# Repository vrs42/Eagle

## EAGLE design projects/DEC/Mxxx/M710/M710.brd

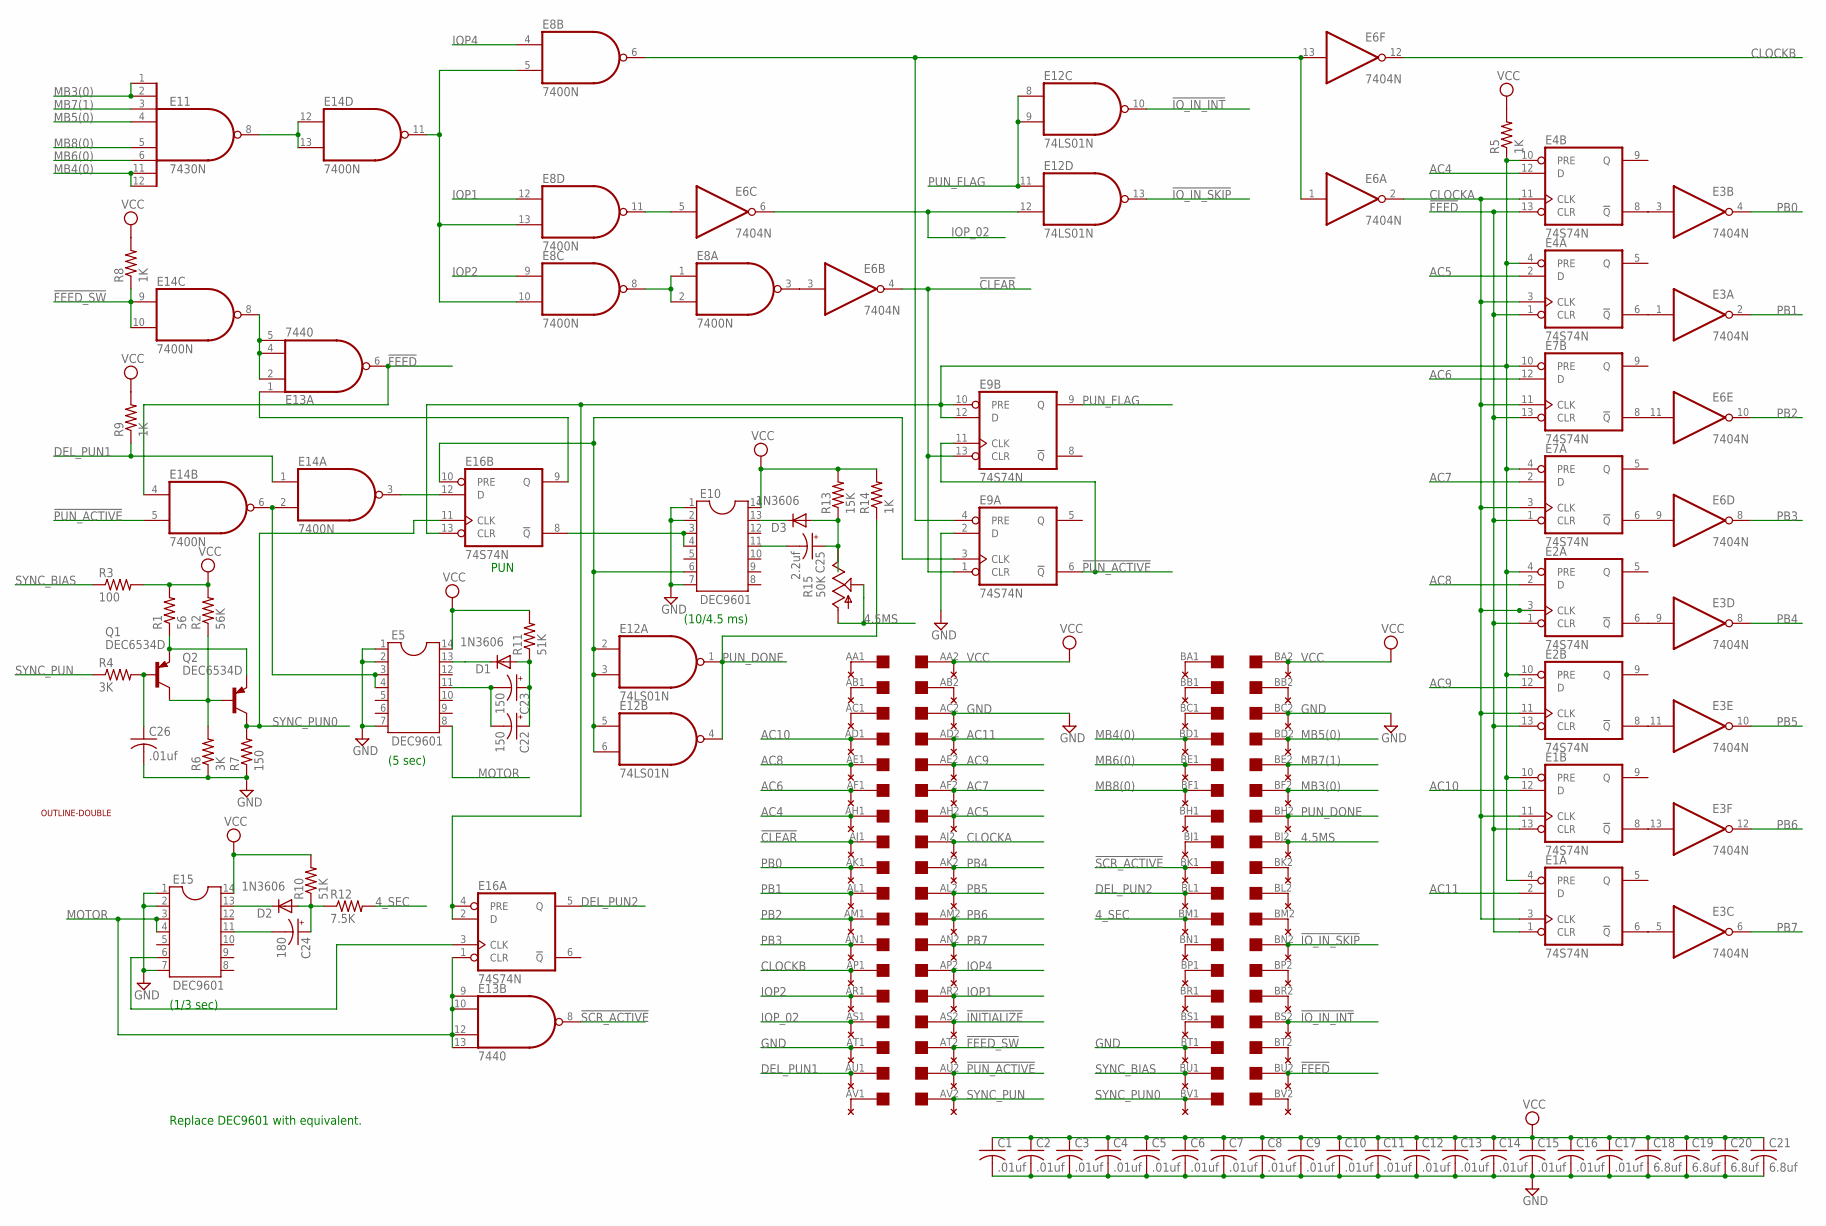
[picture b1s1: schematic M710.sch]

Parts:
C1, C2, C3, C4, C5, C6, C7, C8, C9, C10, C11, C12, C13, C14, C15, C16, C17, C26: .01uf; C050-025X075
C18, C19, C20, C21: 6.8uf; C150-054X183
C22, C23: 150; E5-8,5
C24: 180; E5-8,5
C25: 2.2uf; E5-8,5
D1, D2, D3: 1N3606; DO41-10
E1, E2, E4, E7, E9, E16: 74S74N; DIL14
E3, E6: 7404N; DIL14
E5, E10, E15: DEC9601; DIL14
E8, E14: 7400N; DIL14
E11: 7430N; DIL14
E12: 74LS01N; DIL14
E13: 7440; DIL14
Q1, Q2: DEC6534D; TO92
R1: 56; 0207/7
R2: 56K; 0207/7
R3: 100; 0207/7
R4, R6: 3K; 0207/7
R5, R8, R9, R14: 1K; 0207/7
R7: 150; 0207/7
R10, R11: 51K; 0207/7
R12: 7.5K; 0207/7
R13: 15K; 0207/7
R15: 50K; PT-SPIN
U$1: OUTLINE-DOUBLE; DOUBLE
U$2: DOUBLE; EDGE-CON4
U$5, U$7: THRU-HOLE2; THRU-HOLEB

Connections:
4.5MS: R15.A, R15.S, U$2.BJ2, U$5.J2
4_SEC: R12.2, U$2.BM1, U$5.M1
!CLEAR: E6.4 (O), E9.1 (CLR), E9.13 (CLR), U$2.AJ1, U$7.J1
!FEED: E1.1 (CLR), E1.13 (CLR), E2.1 (CLR), E2.13 (CLR), E4.1 (CLR), E4.13 (CLR), E7.1 (CLR), E7.13 (CLR), E13.6 (O), E14.4 (I0), U$2.BU2, U$5.U2
!FEED_SW: E14.9 (I0), E14.10 (I1), R8.1, U$2.AT2, U$7.T2
!INITIALIZE: U$2.AS2, U$7.S2
!IO_IN_INT: E12.10 (O), U$2.BS2, U$5.S2
!IO_IN_SKIP: E12.13 (O), U$2.BN2, U$5.N2
!PUN_ACTIVE: E9.6 (!Q), E9.11 (CLK), E14.5 (I1), U$2.AU2, U$7.U2
!SCR_ACTIVE: E13.8 (O), U$2.BK1, U$5.K1
AC4: E4.12 (D), U$2.AH1, U$7.H1
AC5: E4.2 (D), U$2.AH2, U$7.H2
AC6: E7.12 (D), U$2.AF1, U$7.F1
AC7: E7.2 (D), U$2.AF2, U$7.F2
AC8: E2.2 (D), U$2.AE1, U$7.E1
AC9: E2.12 (D), U$2.AE2, U$7.E2
AC10: E1.12 (D), U$2.AD1, U$7.D1
AC11: E1.2 (D), U$2.AD2, U$7.D2
CLOCKA: E1.3 (CLK), E1.11 (CLK), E2.3 (CLK), E2.11 (CLK), E4.3 (CLK), E4.11 (CLK), E6.2 (O), E7.3 (CLK), E7.11 (CLK), U$2.AJ2, U$7.J2
CLOCKB: E6.12 (O), U$2.AP1, U$7.P1
DEL_PUN1: E14.1 (I0), R9.1, U$2.AU1, U$7.U1
DEL_PUN2: E16.5 (Q), U$2.BL1, U$5.L1
GND: C1.2, C2.2, C3.2, C4.2, C5.2, C6.2, C7.2, C8.2, C9.2, C10.2, C11.2, C12.2, C13.2, C14.2, C15.2, C16.2, C17.2, C18.2, C19.2, C20.2, C21.2, C26.2, E1.7 (GND), E2.7 (GND), E3.7 (GND), E4.7 (GND), E5.1, E5.2, E5.7, E6.7 (GND), E7.7 (GND), E8.7 (GND), E9.2 (D), E9.7 (GND), E10.1, E10.2, E10.7, E11.7 (GND), E12.7 (GND), E13.7 (GND), E14.7 (GND), E15.1, E15.2, E15.7, E16.7 (GND), R6.1, R7.1, U$2.AC2, U$2.AT1, U$2.BC2, U$2.BT1, U$5.C2, U$5.T1, U$7.C2, U$7.T1
IOP1: E8.12 (I0), U$2.AR2, U$7.R2
IOP2: E8.9 (I0), U$2.AR1, U$7.R1
IOP4: E8.4 (I0), U$2.AP2, U$7.P2
IOP_02: E6.6 (O), E12.12 (I1), U$2.AS1, U$7.S1
MB3(0): E11.1 (I0), E11.2 (I1), U$2.BF2, U$5.F2
MB4(0): E11.11 (I6), E11.12 (I7), U$2.BD1, U$5.D1
MB5(0): E11.4 (I3), U$2.BD2, U$5.D2
MB6(0): E11.6 (I5), U$2.BE1, U$5.E1
MB7(1): E11.3 (I2), U$2.BE2, U$5.E2
MB8(0): E11.5 (I4), U$2.BF1, U$5.F1
MOTOR: E5.8, E13.9 (I0), E13.10 (I1), E13.12 (I2), E13.13 (I3), E15.3, E15.4, E16.1 (CLR)
unnamed: U$2.AB2, U$7.B2
unnamed: E3.3 (I), E4.8 (!Q)
unnamed: E3.1 (I), E4.6 (!Q)
unnamed: E6.1 (I), E6.13 (I), E8.6 (O), E9.4 (PRE)
unnamed: E11.8 (O), E14.12 (I0), E14.13 (I1)
unnamed: E6.3 (I), E8.3 (O)
unnamed: E8.1 (I0), E8.2 (I1), E8.8 (O)
unnamed: E8.5 (I1), E8.10 (I1), E8.13 (I1), E14.11 (O)
unnamed: E2.6 (!Q), E3.9 (I)
unnamed: E2.8 (!Q), E3.11 (I)
unnamed: E1.8 (!Q), E3.13 (I)
unnamed: E1.6 (!Q), E3.5 (I)
unnamed: E6.11 (I), E7.8 (!Q)
unnamed: E6.9 (I), E7.6 (!Q)
unnamed: U$2.AV1, U$7.V1
unnamed: E6.5 (I), E8.11 (O)
unnamed: U$2.AC1, U$7.C1
unnamed: U$2.AB1, U$7.B1
unnamed: Q1.1 (C), Q2.2 (B), R2.1, R6.2
unnamed: U$2.BS1, U$5.S1
unnamed: U$2.BR1, U$5.R1
unnamed: U$2.BP1, U$5.P1
unnamed: U$2.BN1, U$5.N1
unnamed: U$2.AA1, U$7.A1
unnamed: U$2.BJ1, U$5.J1
unnamed: U$2.BH1, U$5.H1
unnamed: U$2.BC1, U$5.C1
unnamed: U$2.BB1, U$5.B1
unnamed: U$2.BA1, U$5.A1
unnamed: U$2.BV2, U$5.V2
unnamed: U$2.BT2, U$5.T2
unnamed: U$2.BR2, U$5.R2
unnamed: U$2.BP2, U$5.P2
unnamed: Q1.3 (E), Q2.3 (E), R1.1
unnamed: U$2.BM2, U$5.M2
unnamed: C26.1, Q1.2 (B), R4.2
unnamed: U$2.BL2, U$5.L2
unnamed: C24.-, E15.11
unnamed: E13.2 (I1), E13.4 (I2), E13.5 (I3), E14.8 (O)
unnamed: U$2.BK2, U$5.K2
unnamed: U$2.BB2, U$5.B2
unnamed: E1.4 (PRE), E1.10 (PRE), E2.4 (PRE), E2.10 (PRE), E4.4 (PRE), E4.10 (PRE), E7.4 (PRE), E7.10 (PRE), E9.10 (PRE), E9.12 (D), E16.2 (D), E16.4 (PRE), E16.13 (CLR), R5.1
unnamed: C25.-, E10.11
unnamed: E13.1 (I0), E16.9 (Q)
unnamed: E14.3 (O), E16.12 (D)
unnamed: E5.3, E5.4, E14.2 (I1), E14.6 (O)
unnamed: C22.-, C23.-, E5.11
unnamed: D1.C, E5.13
unnamed: C22.+, C23.+, D1.A, R11.1
unnamed: D2.C, E15.13
unnamed: C24.+, D2.A, R10.1, R12.1
unnamed: E15.6, E16.3 (CLK)
unnamed: D3.C, E10.13
unnamed: C25.+, D3.A, R13.1, R15.E
unnamed: E10.3, E10.4, E16.8 (!Q)
unnamed: E9.3 (CLK), E10.6, E12.2 (I0), E12.3 (I1), E12.5 (I0), E12.6 (I1), E16.10 (PRE)
PB0: E3.4 (O), U$2.AK1, U$7.K1
PB1: E3.2 (O), U$2.AL1, U$7.L1
PB2: E6.10 (O), U$2.AM1, U$7.M1
PB3: E6.8 (O), U$2.AN1, U$7.N1
PB4: E3.8 (O), U$2.AK2, U$7.K2
PB5: E3.10 (O), U$2.AL2, U$7.L2
PB6: E3.12 (O), U$2.AM2, U$7.M2
PB7: E3.6 (O), U$2.AN2, U$7.N2
PUN_DONE: E12.1 (O), E12.4 (O), R14.1, U$2.BH2, U$5.H2
PUN_FLAG: E9.9 (Q), E12.8 (I0), E12.9 (I1), E12.11 (I0)
SYNC_BIAS: R3.1, U$2.BU1, U$5.U1
SYNC_PUN: R4.1, U$2.AV2, U$7.V2
SYNC_PUN0: E16.11 (CLK), Q2.1 (C), R7.2, U$2.BV1, U$5.V1
VCC: C1.1, C2.1, C3.1, C4.1, C5.1, C6.1, C7.1, C8.1, C9.1, C10.1, C11.1, C12.1, C13.1, C14.1, C15.1, C16.1, C17.1, C18.1, C19.1, C20.1, C21.1, E1.14 (VCC), E2.14 (VCC), E3.14 (VCC), E4.14 (VCC), E5.14, E6.14 (VCC), E7.14 (VCC), E8.14 (VCC), E9.14 (VCC), E10.14, E11.14 (VCC), E12.14 (VCC), E13.14 (VCC), E14.14 (VCC), E15.14, E16.14 (VCC), R1.2, R2.2, R3.2, R5.2, R8.2, R9.2, R10.2, R11.2, R13.2, R14.2, U$2.AA2, U$2.BA2, U$5.A2, U$7.A2

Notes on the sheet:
(5 sec)
(1/3 sec)
(10/4.5 ms)
PUN
Replace DEC9601 with equivalent.

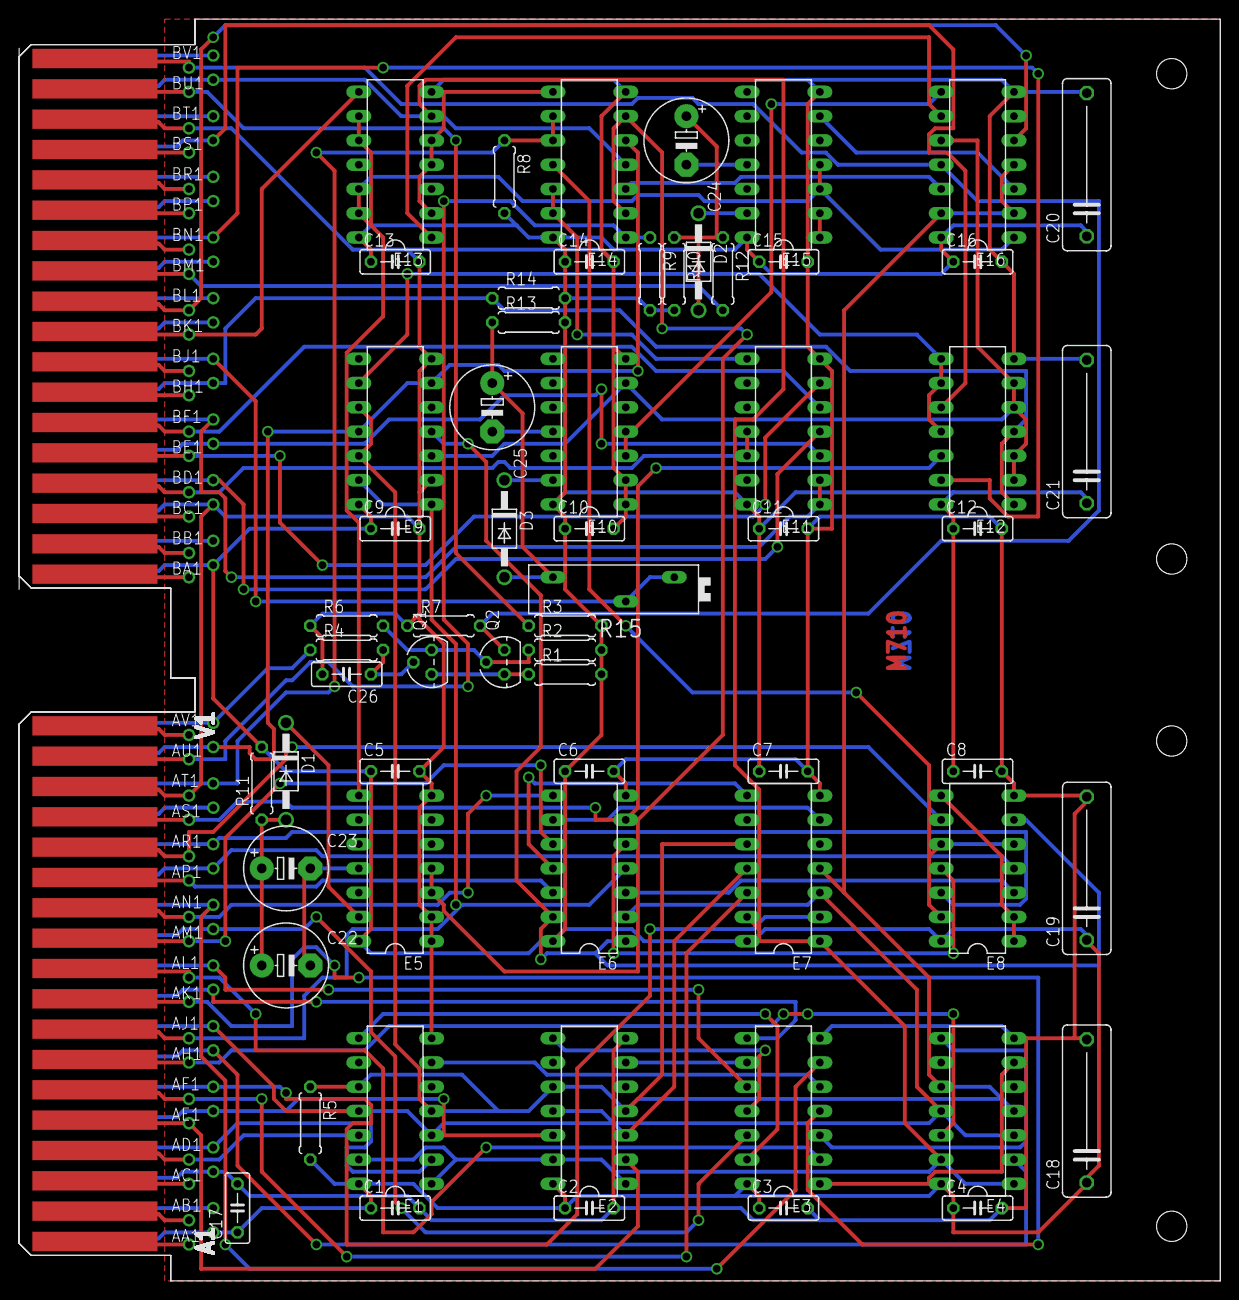
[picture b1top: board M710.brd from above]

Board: 2 copper layers, 125.7 x 132.1 mm, 66 parts (0 on the bottom side), 104 nets.

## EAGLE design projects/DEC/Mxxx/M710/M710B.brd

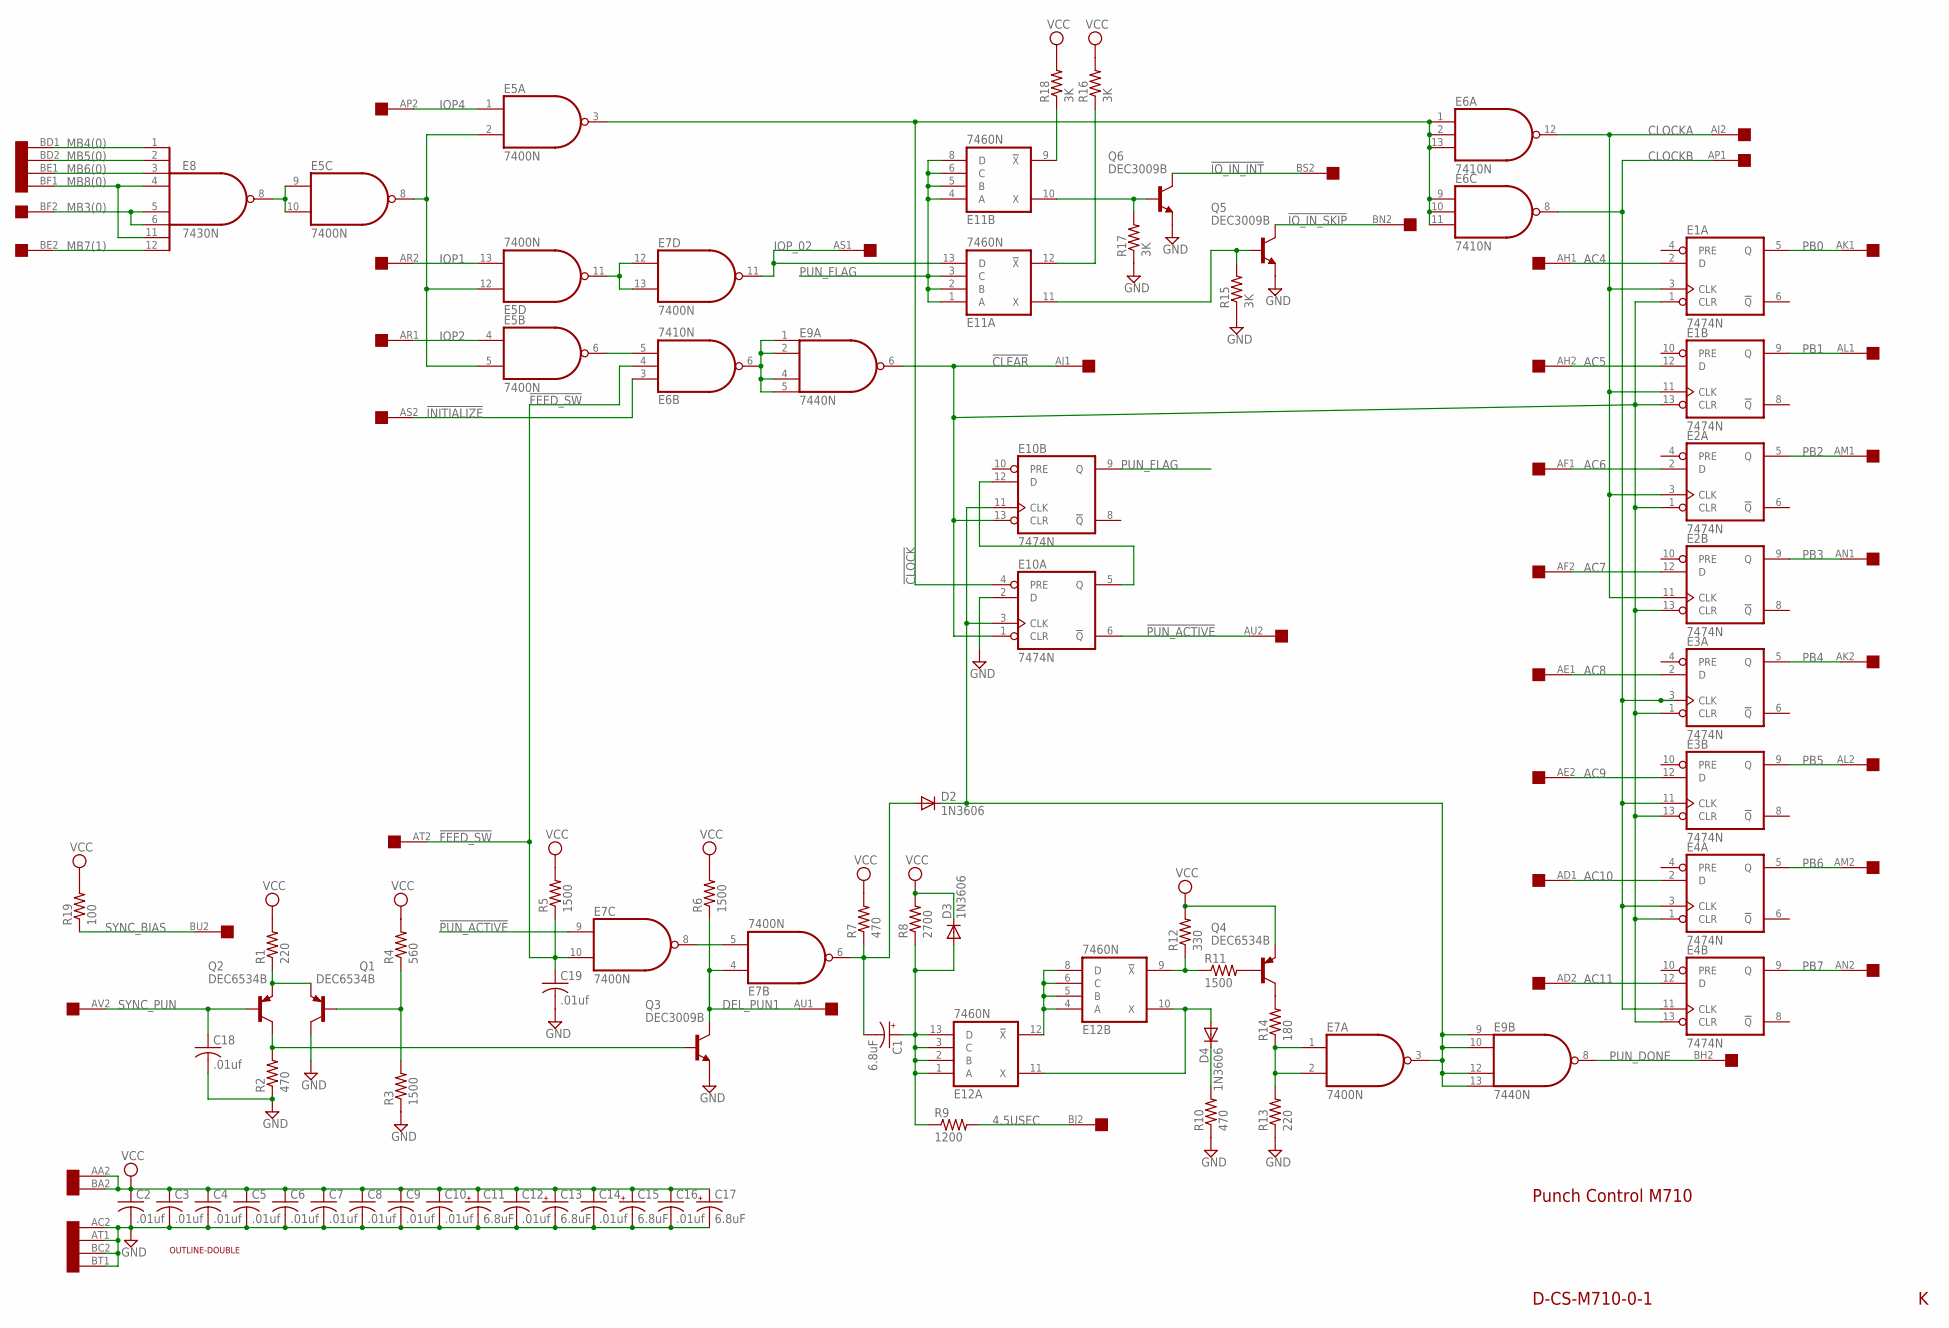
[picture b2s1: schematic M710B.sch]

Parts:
C1, C11, C13, C15, C17: 6.8uF; E15-5
C2, C3, C4, C5, C6, C7, C8, C9, C10, C12, C14, C16, C18, C19: .01uf; C075-032X103
D2, D3, D4: 1N3606; SOD61B
E1, E2, E3, E4, E10: 7474N; DIL14
E5, E7: 7400N; DIL14
E6: 7410N; DIL14
E8: 7430N; DIL14
E9: 7440N; DIL14
E11, E12: 7460N; DIL14
Q1, Q2, Q4: DEC6534B; TO92-EBC
Q3, Q5, Q6: DEC3009B; TO92-EBC
R1, R13: 220; 0207/15
R2, R7, R10: 470; 0207/15
R3, R5, R6, R11: 1500; 0207/15
R4: 560; 0207/15
R8: 2700; 0207/15
R9: 1200; 0207/15
R12: 330; 0207/15
R14: 180; 0207/15
R15, R16, R17, R18: 3K; 0207/15
R19: 100; 0207/15
U$1: OUTLINE-DOUBLE; DOUBLE
U$2: DOUBLE; EDGE-CON4

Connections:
4.5USEC: R9.2, U$2.BJ2
!CLEAR: E1.1 (CLR), E1.13 (CLR), E2.1 (CLR), E2.13 (CLR), E3.1 (CLR), E3.13 (CLR), E4.1 (CLR), E4.13 (CLR), E9.6 (O), E10.1 (CLR), E10.13 (CLR), U$2.AJ1
!CLOCK: E5.3 (O), E6.1 (I0), E6.2 (I1), E6.9 (I0), E6.10 (I1), E6.11 (I2), E6.13 (I2), E10.4 (PRE)
!FEED_SW: C19.1, E6.4 (I1), E7.10 (I1), R5.1, U$2.AT2
!INITIALIZE: E6.3 (I0), U$2.AS2
!IO_IN_INT: Q6.C, U$2.BS2
!IO_IN_SKIP: Q5.C, U$2.BN2
!PUN_ACTIVE: E7.9 (I0), E10.6 (!Q), U$2.AU2
AC4: E1.2 (D), U$2.AH1
AC5: E1.12 (D), U$2.AH2
AC6: E2.2 (D), U$2.AF1
AC7: E2.12 (D), U$2.AF2
AC8: E3.2 (D), U$2.AE1
AC9: E3.12 (D), U$2.AE2
AC10: E4.2 (D), U$2.AD1
AC11: E4.12 (D), U$2.AD2
CLOCKA: E1.3 (CLK), E1.11 (CLK), E2.3 (CLK), E2.11 (CLK), E6.12 (O), U$2.AJ2
CLOCKB: E3.3 (CLK), E3.11 (CLK), E4.3 (CLK), E4.11 (CLK), E6.8 (O), U$2.AP1
DEL_PUN1: E7.4 (I0), Q3.C, R6.1, U$2.AU1
GND: C2.2, C3.2, C4.2, C5.2, C6.2, C7.2, C8.2, C9.2, C10.2, C11.-, C12.2, C13.-, C14.2, C15.-, C16.2, C17.-, C18.2, C19.2, E1.7 (GND), E2.7 (GND), E3.7 (GND), E4.7 (GND), E5.7 (GND), E6.7 (GND), E7.7 (GND), E8.7 (GND), E9.7 (GND), E10.2 (D), E10.7 (GND), E11.7 (GND), E12.7 (GND), Q1.C, Q3.E, Q5.E, Q6.E, R2.1, R3.1, R10.1, R13.1, R15.1, R17.1, U$2.AC2, U$2.AT1, U$2.BC2, U$2.BT1
IOP1: E5.13 (I1), U$2.AR2
IOP2: E5.4 (I0), U$2.AR1
IOP4: E5.1 (I0), U$2.AP2
IOP_02: E7.11 (O), E11.13 (D), U$2.AS1
MB3(0): E8.5 (I4), E8.6 (I5), U$2.BF2
MB4(0): E8.1 (I0), U$2.BD1
MB5(0): E8.2 (I1), U$2.BD2
MB6(0): E8.3 (I2), U$2.BE1
MB7(1): E8.12 (I7), U$2.BE2
MB8(0): E8.4 (I3), E8.11 (I6), U$2.BF1
unnamed: D2.C, E7.3 (O), E9.9 (I0), E9.10 (I1), E9.12 (I2), E9.13 (I3), E10.3 (CLK), E10.11 (CLK)
unnamed: E6.6 (O), E9.1 (I0), E9.2 (I1), E9.4 (I2), E9.5 (I3)
unnamed: E12.4 (A), E12.5 (B), E12.6 (C), E12.8 (D), E12.12 (!X)
unnamed: C1.+, D3.A, E12.1 (A), E12.2 (B), E12.3 (C), E12.13 (D), R8.1, R9.1
unnamed: E5.9 (I0), E5.10 (I1), E8.8 (O)
unnamed: D4.A, E12.10 (X), E12.11 (X)
unnamed: E5.6 (O), E6.5 (I2)
unnamed: E5.2 (I1), E5.5 (I1), E5.8 (O), E5.12 (I0)
unnamed: E11.9 (!X), R18.1
unnamed: E11.12 (!X), R16.1
unnamed: E11.11 (X), Q5.B, R15.2
unnamed: E11.10 (X), Q6.B, R17.2
unnamed: D4.C, R10.2
unnamed: Q4.B, R11.2
unnamed: E5.11 (O), E7.12 (I0), E7.13 (I1)
unnamed: Q1.B, R3.2, R4.1
unnamed: Q2.C, Q3.B, R2.2
unnamed: E12.9 (!X), R11.1, R12.1
unnamed: Q4.C, R14.2
unnamed: E7.1 (I0), E7.2 (I1), R13.2, R14.1
unnamed: E7.5 (I1), E7.8 (O)
unnamed: C1.-, D2.A, E7.6 (O), R7.1
unnamed: E10.5 (Q), E10.12 (D)
unnamed: Q1.E, Q2.E, R1.1
PB0: E1.5 (Q), U$2.AK1
PB1: E1.9 (Q), U$2.AL1
PB2: E2.5 (Q), U$2.AM1
PB3: E2.9 (Q), U$2.AN1
PB4: E3.5 (Q), U$2.AK2
PB5: E3.9 (Q), U$2.AL2
PB6: E4.5 (Q), U$2.AM2
PB7: E4.9 (Q), U$2.AN2
PUN_DONE: E9.8 (O), U$2.BH2
PUN_FLAG: E10.9 (Q), E11.1 (A), E11.2 (B), E11.3 (C), E11.4 (A), E11.5 (B), E11.6 (C), E11.8 (D)
SYNC_BIAS: R19.1, U$2.BU2
SYNC_PUN: C18.1, Q2.B, U$2.AV2
VCC: C2.1, C3.1, C4.1, C5.1, C6.1, C7.1, C8.1, C9.1, C10.1, C11.+, C12.1, C13.+, C14.1, C15.+, C16.1, C17.+, D3.C, E1.14 (VCC), E2.14 (VCC), E3.14 (VCC), E4.14 (VCC), E5.14 (VCC), E6.14 (VCC), E7.14 (VCC), E8.14 (VCC), E9.14 (VCC), E10.14 (VCC), E11.14 (VCC), E12.14 (VCC), Q4.E, R1.2, R4.2, R5.2, R6.2, R7.2, R8.2, R12.2, R16.2, R18.2, R19.2, U$2.AA2, U$2.BA2

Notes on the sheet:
Punch Control M710
D-CS-M710-0-1

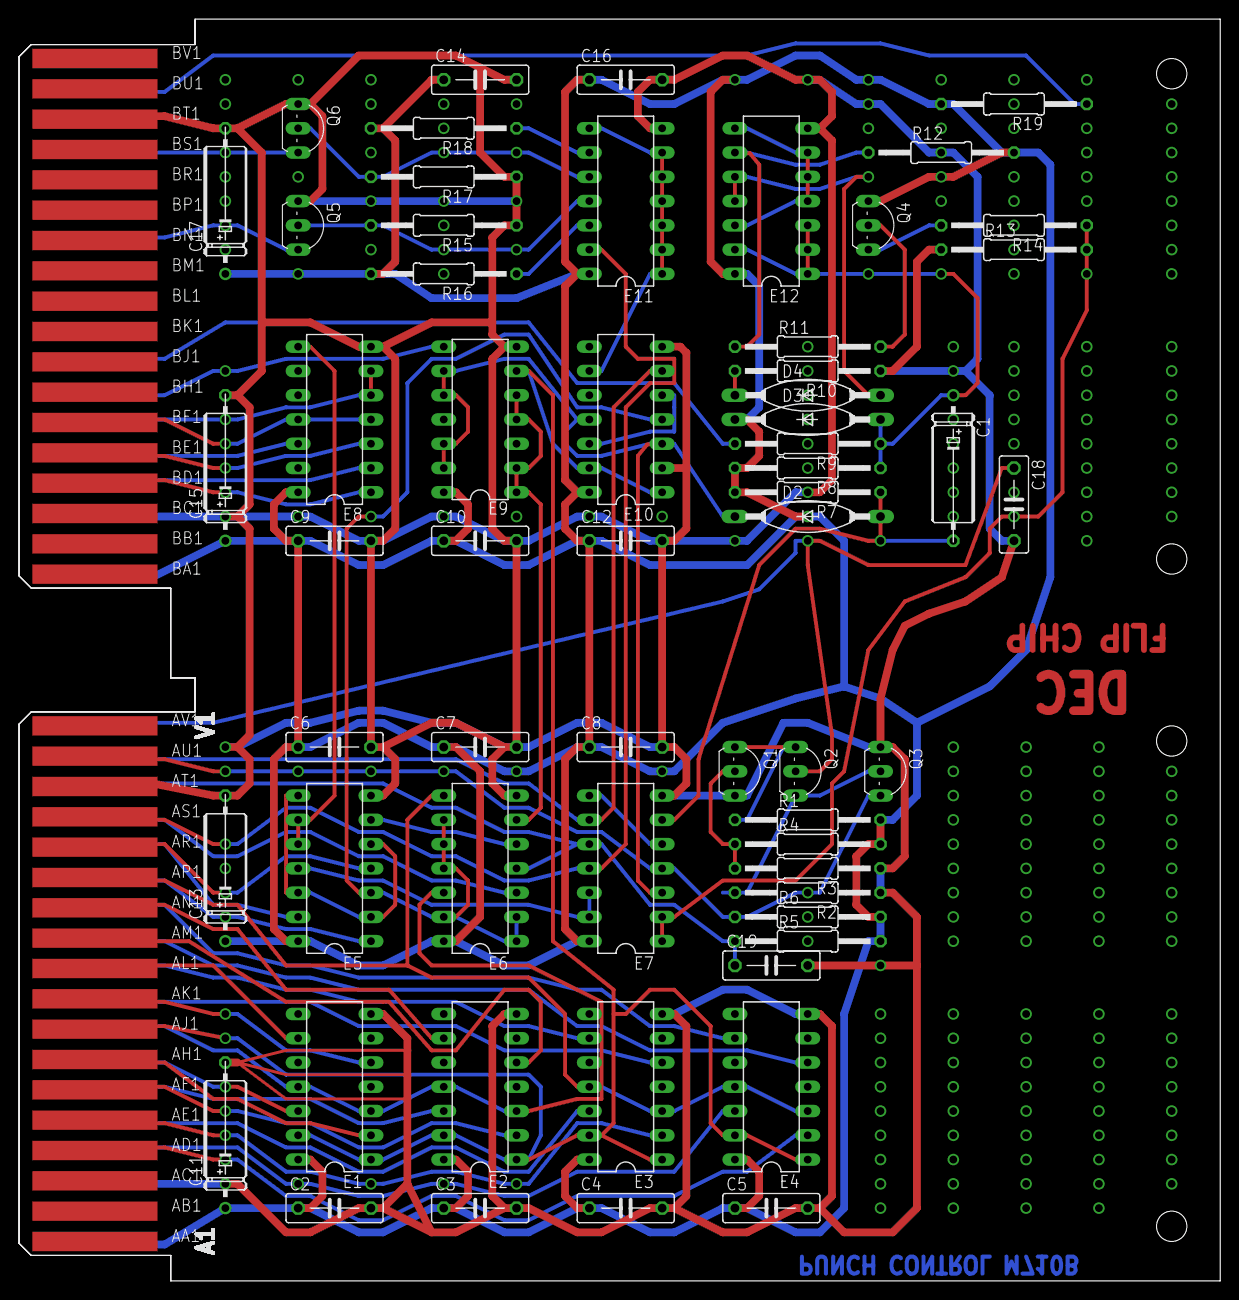
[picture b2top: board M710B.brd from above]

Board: 2 copper layers, 125.7 x 132.1 mm, 61 parts (0 on the bottom side), 67 nets.

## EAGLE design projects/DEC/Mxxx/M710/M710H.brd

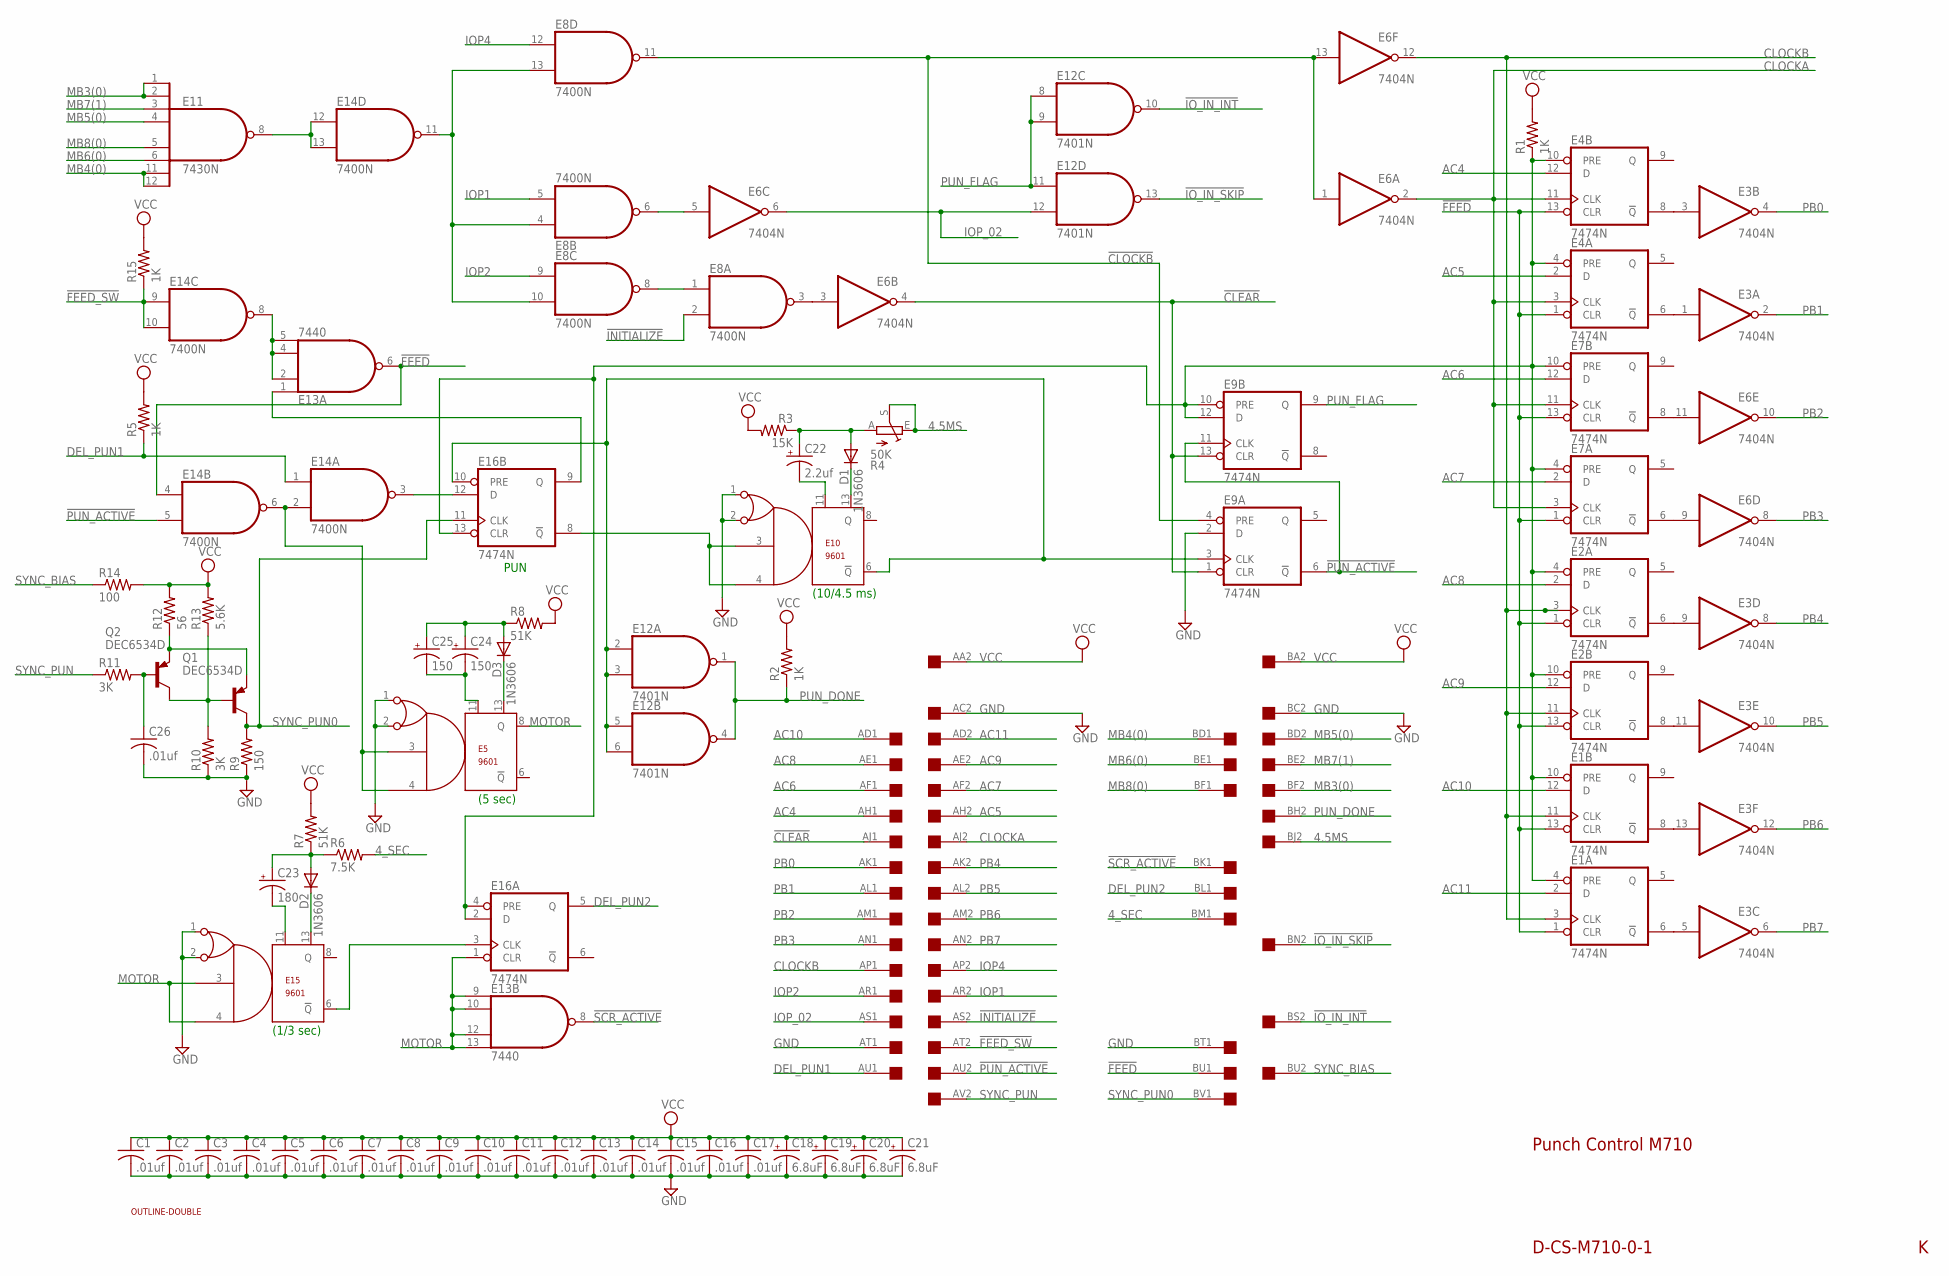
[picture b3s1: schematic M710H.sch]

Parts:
C1, C2, C3, C4, C5, C6, C7, C8, C9, C10, C11, C12, C13, C14, C15, C16, C17, C26: .01uf; C050-025X075
C18, C19, C20, C21: 6.8uF; E12-8
C22: 2.2uf; E15-5
C23: 180; E12-8
C24, C25: 150; E22-6
D1, D2, D3: 1N3606; DO41-10
E1, E2, E4, E7, E9, E16: 7474N; DIL14
E3, E6: 7404N; DIL14
E5, E10, E15: 9601; DIL14
E8, E14: 7400N; DIL14
E11: 7430N; DIL14
E12: 7401N; DIL14
E13: 7440; DIL14
Q1, Q2: DEC6534D; TO5
R1, R2, R5, R15: 1K; 0207/10
R3: 15K; 0207/10
R4: 50K; RJ6
R6: 7.5K; 0207/10
R7, R8: 51K; 0207/10
R9: 150; 0207/10
R10, R11: 3K; 0207/10
R12: 56; 0207/10
R13: 5.6K; 0207/10
R14: 100; 0207/10
U$1: OUTLINE-DOUBLE; DOUBLE
U$2: DOUBLE; EDGE-CON4

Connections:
4.5MS: R4.E, R4.S, U$2.BJ2
4_SEC: R6.2, U$2.BM1
!CLEAR: E6.4 (O), E9.1 (CLR), E9.13 (CLR), U$2.AJ1
!CLOCKB: E6.1 (I), E6.13 (I), E8.11 (O), E9.4 (PRE)
!FEED: E1.1 (CLR), E1.13 (CLR), E2.1 (CLR), E2.13 (CLR), E4.1 (CLR), E4.13 (CLR), E7.1 (CLR), E7.13 (CLR), E13.6 (O), E14.4 (I0), U$2.BU1
!FEED_SW: E14.9 (I0), E14.10 (I1), R15.1, U$2.AT2
!INITIALIZE: E8.2 (I1), U$2.AS2
!IO_IN_INT: E12.10 (O), U$2.BS2
!IO_IN_SKIP: E12.13 (O), U$2.BN2
!PUN_ACTIVE: E9.6 (!Q), E9.11 (CLK), E14.5 (I1), U$2.AU2
!SCR_ACTIVE: E13.8 (O), U$2.BK1
AC4: E4.12 (D), U$2.AH1
AC5: E4.2 (D), U$2.AH2
AC6: E7.12 (D), U$2.AF1
AC7: E7.2 (D), U$2.AF2
AC8: E2.2 (D), U$2.AE1
AC9: E2.12 (D), U$2.AE2
AC10: E1.12 (D), U$2.AD1
AC11: E1.2 (D), U$2.AD2
CLOCKA: E4.3 (CLK), E4.11 (CLK), E6.2 (O), E7.3 (CLK), E7.11 (CLK), U$2.AJ2
CLOCKB: E1.3 (CLK), E1.11 (CLK), E2.3 (CLK), E2.11 (CLK), E6.12 (O), U$2.AP1
DEL_PUN1: E14.1 (I0), R5.1, U$2.AU1
DEL_PUN2: E16.5 (Q), U$2.BL1
GND: C1.2, C2.2, C3.2, C4.2, C5.2, C6.2, C7.2, C8.2, C9.2, C10.2, C11.2, C12.2, C13.2, C14.2, C15.2, C16.2, C17.2, C18.-, C19.-, C20.-, C21.-, C26.2, E1.7 (GND), E2.7 (GND), E3.7 (GND), E4.7 (GND), E5.1, E5.2, E5.7 (GND), E6.7 (GND), E7.7 (GND), E8.7 (GND), E9.2 (D), E9.7 (GND), E10.1, E10.2, E10.7 (GND), E11.7 (GND), E12.7 (GND), E13.7 (GND), E14.7 (GND), E15.1, E15.2, E15.7 (GND), E16.7 (GND), R9.1, R10.1, U$2.AC2, U$2.AT1, U$2.BC2, U$2.BT1
IOP1: E8.5 (I1), U$2.AR2
IOP2: E8.9 (I0), U$2.AR1
IOP4: E8.12 (I0), U$2.AP2
IOP_02: E6.6 (O), E12.12 (I1), U$2.AS1
MB3(0): E11.1 (I0), E11.2 (I1), U$2.BF2
MB4(0): E11.11 (I6), E11.12 (I7), U$2.BD1
MB5(0): E11.4 (I3), U$2.BD2
MB6(0): E11.6 (I5), U$2.BE1
MB7(1): E11.3 (I2), U$2.BE2
MB8(0): E11.5 (I4), U$2.BF1
MOTOR: E5.8 (Q), E13.9 (I0), E13.10 (I1), E13.12 (I2), E13.13 (I3), E15.3, E15.4, E16.1 (CLR)
unnamed: E5.3, E5.4, E14.2 (I1), E14.6 (O)
unnamed: E3.3 (I), E4.8 (!Q)
unnamed: E3.1 (I), E4.6 (!Q)
unnamed: E10.3, E10.4, E16.8 (!Q)
unnamed: E11.8 (O), E14.12 (I0), E14.13 (I1)
unnamed: E6.3 (I), E8.3 (O)
unnamed: E8.1 (I0), E8.8 (O)
unnamed: E8.4 (I0), E8.10 (I1), E8.13 (I1), E14.11 (O)
unnamed: E2.6 (!Q), E3.9 (I)
unnamed: E2.8 (!Q), E3.11 (I)
unnamed: E1.8 (!Q), E3.13 (I)
unnamed: E1.6 (!Q), E3.5 (I)
unnamed: E6.11 (I), E7.8 (!Q)
unnamed: E6.9 (I), E7.6 (!Q)
unnamed: E9.3 (CLK), E10.6 (!Q), E12.2 (I0), E12.3 (I1), E12.5 (I0), E12.6 (I1), E16.10 (PRE)
unnamed: E6.5 (I), E8.6 (O)
unnamed: Q1.2 (B), Q2.3 (C), R10.2, R13.1
unnamed: E1.4 (PRE), E1.10 (PRE), E2.4 (PRE), E2.10 (PRE), E4.4 (PRE), E4.10 (PRE), E7.4 (PRE), E7.10 (PRE), E9.10 (PRE), E9.12 (D), E16.2 (D), E16.4 (PRE), E16.13 (CLR), R1.1
unnamed: Q1.1 (E), Q2.1 (E), R12.1
unnamed: C26.1, Q2.2 (B), R11.2
unnamed: C23.-, E15.11
unnamed: E13.2 (I1), E13.4 (I2), E13.5 (I3), E14.8 (O)
unnamed: C22.-, E10.11
unnamed: E13.1 (I0), E16.9 (Q)
unnamed: E14.3 (O), E16.12 (D)
unnamed: C24.-, C25.-, E5.11
unnamed: D3.C, E5.13
unnamed: C24.+, C25.+, D3.A, R8.1
unnamed: D2.C, E15.13
unnamed: C23.+, D2.A, R6.1, R7.1
unnamed: E15.6 (!Q), E16.3 (CLK)
unnamed: D1.C, E10.13
unnamed: C22.+, D1.A, R3.1, R4.A
PB0: E3.4 (O), U$2.AK1
PB1: E3.2 (O), U$2.AL1
PB2: E6.10 (O), U$2.AM1
PB3: E6.8 (O), U$2.AN1
PB4: E3.8 (O), U$2.AK2
PB5: E3.10 (O), U$2.AL2
PB6: E3.12 (O), U$2.AM2
PB7: E3.6 (O), U$2.AN2
PUN_DONE: E12.1 (O), E12.4 (O), R2.1, U$2.BH2
PUN_FLAG: E9.9 (Q), E12.8 (I0), E12.9 (I1), E12.11 (I0)
SYNC_BIAS: R14.1, U$2.BU2
SYNC_PUN: R11.1, U$2.AV2
SYNC_PUN0: E16.11 (CLK), Q1.3 (C), R9.2, U$2.BV1
VCC: C1.1, C2.1, C3.1, C4.1, C5.1, C6.1, C7.1, C8.1, C9.1, C10.1, C11.1, C12.1, C13.1, C14.1, C15.1, C16.1, C17.1, C18.+, C19.+, C20.+, C21.+, E1.14 (VCC), E2.14 (VCC), E3.14 (VCC), E4.14 (VCC), E5.14 (VCC), E6.14 (VCC), E7.14 (VCC), E8.14 (VCC), E9.14 (VCC), E10.14 (VCC), E11.14 (VCC), E12.14 (VCC), E13.14 (VCC), E14.14 (VCC), E15.14 (VCC), E16.14 (VCC), R1.2, R2.2, R3.2, R5.2, R7.2, R8.2, R12.2, R13.2, R14.2, R15.2, U$2.AA2, U$2.BA2

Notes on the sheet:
(5 sec)
(1/3 sec)
(10/4.5 ms)
PUN
Punch Control M710
D-CS-M710-0-1

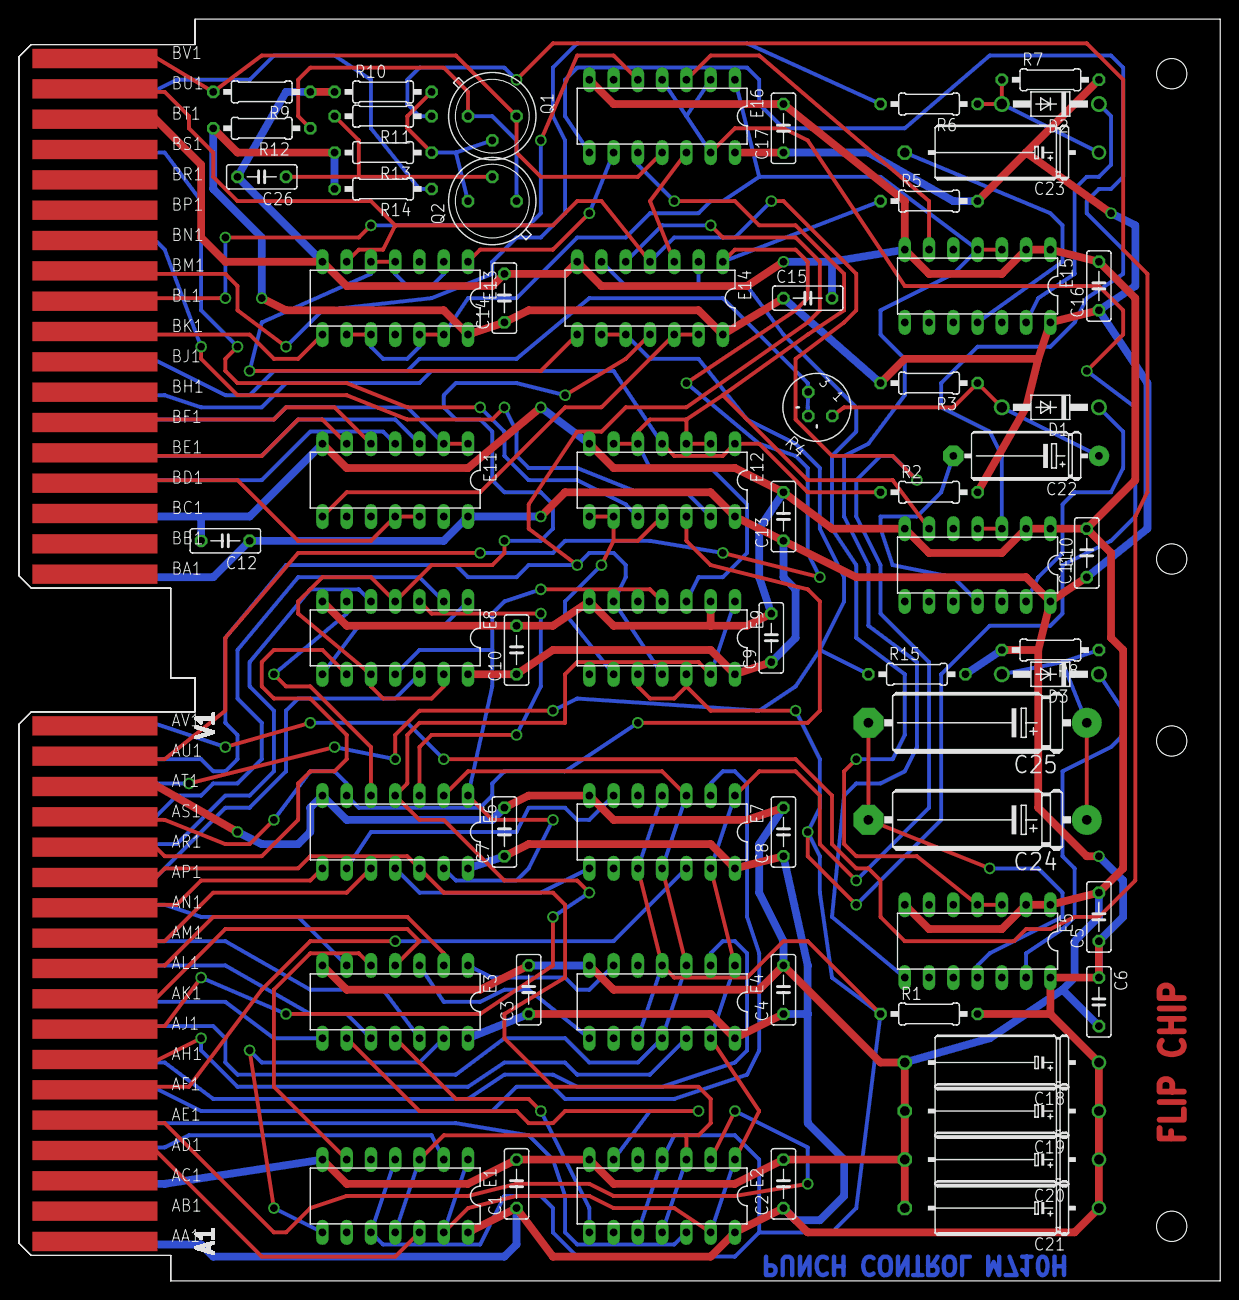
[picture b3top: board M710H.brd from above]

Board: 2 copper layers, 125.7 x 132.1 mm, 65 parts (0 on the bottom side), 82 nets.

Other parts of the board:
U$3: FLIPCHIP
